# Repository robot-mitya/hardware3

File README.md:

# hardware3
Mitya's III KiCad files

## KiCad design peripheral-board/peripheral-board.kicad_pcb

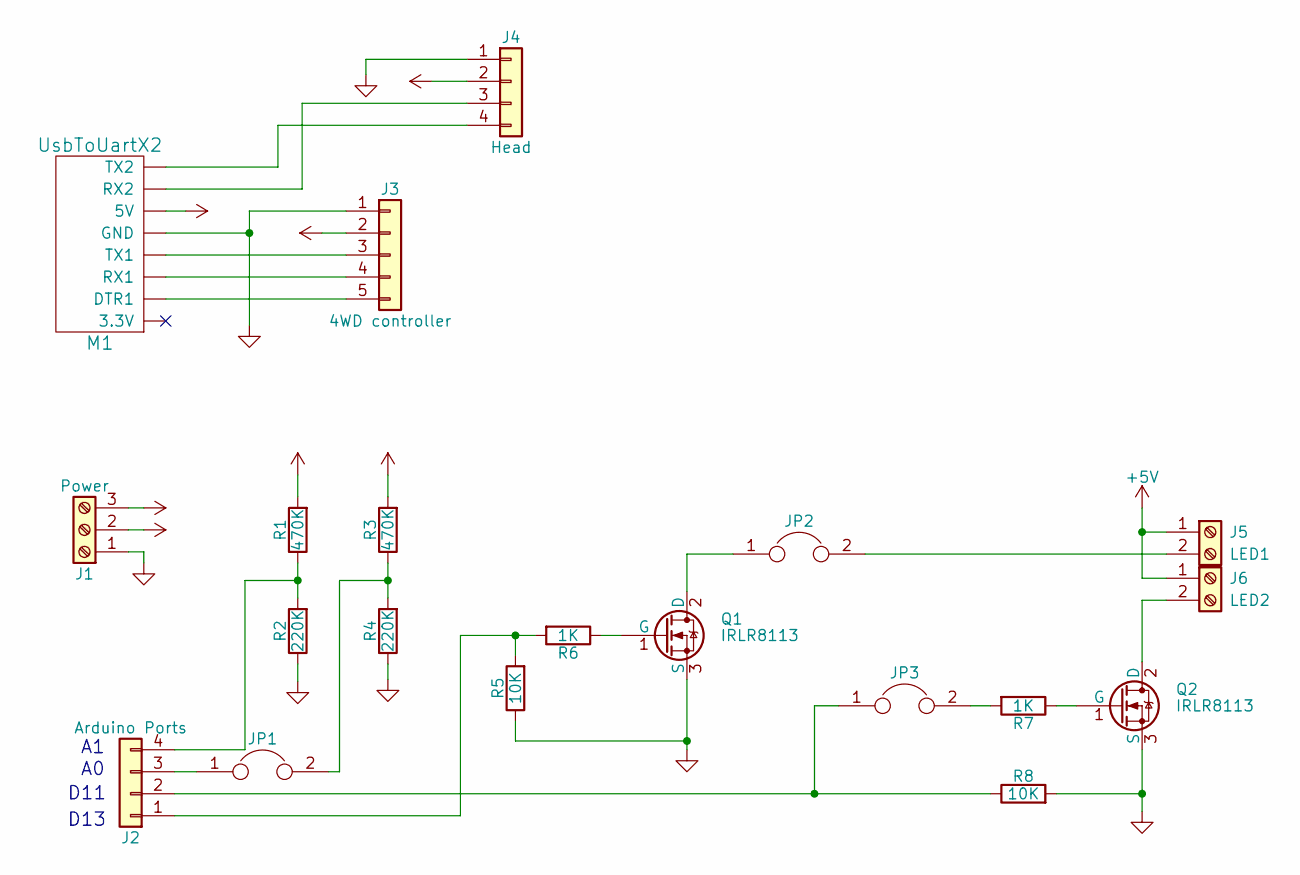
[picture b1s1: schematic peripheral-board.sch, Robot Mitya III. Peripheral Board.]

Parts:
J1: Power; TerminalBlock_Pheonix_PT-3.5mm_3pol
J2: Arduino Ports; JST_EH_B04B-EH-A_04x2.50mm_Straight
J3: 4WD controller; JST_EH_B05B-EH-A_05x2.50mm_Straight
J4: Head; JST_EH_B04B-EH-A_04x2.50mm_Straight
J5: LED1; TerminalBlock_Pheonix_PT-3.5mm_2pol
J6: LED2; TerminalBlock_Pheonix_PT-3.5mm_2pol
JP1, JP2, JP3: Jumper; WireConnection_0.80mmDrill
M1: UsbToUartX2
Q1, Q2: IRLR8113; TO-252-2_Rectifier
R1, R3: 470K; R_1206_HandSoldering
R2, R4: 220K; R_1206_HandSoldering
R5, R8: 10K; R_1206_HandSoldering
R6, R7: 1K; R_1206_HandSoldering

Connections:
+5V: J1.2, J3.2, J5.1, J6.1, M1.6 (5V), R1.2
+7.4V: J1.3, J4.2, R3.2
GND: J1.1, J3.1, J4.1, M1.5 (GND), Q1.3 (S), Q2.3 (S), R2.1, R4.1, R5.1, R8.2
unnamed: J2.1, R5.2, R6.2
unnamed: J2.2, JP3.1, R8.1
unnamed: J2.3, JP1.1
unnamed: J2.4, R1.1, R2.2
unnamed: J3.3, M1.4 (TX1)
unnamed: J3.4, M1.3 (RX1)
unnamed: J3.5, M1.2 (DTR1)
unnamed: J4.3, M1.7 (RX2)
unnamed: J4.4, M1.8 (TX2)
unnamed: J5.2, JP2.2
unnamed: J6.2, Q2.2 (D)
unnamed: JP1.2, R3.1, R4.2
unnamed: JP2.1, Q1.2 (D)
unnamed: JP3.2, R7.2
unnamed: Q1.1 (G), R6.1
unnamed: Q2.1 (G), R7.1

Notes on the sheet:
D13
D11

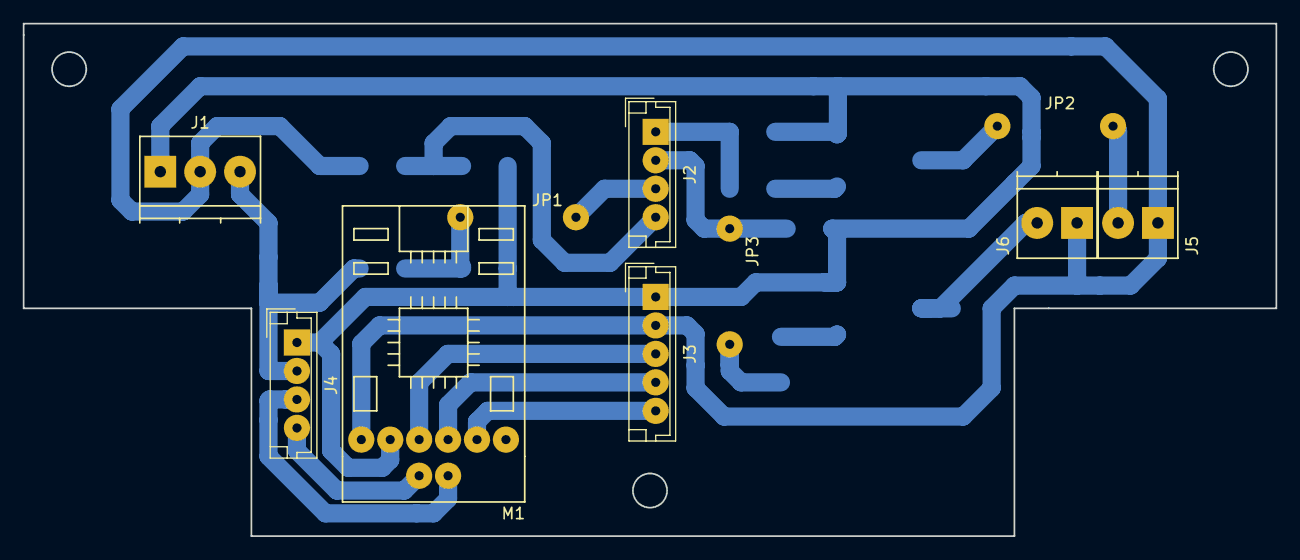
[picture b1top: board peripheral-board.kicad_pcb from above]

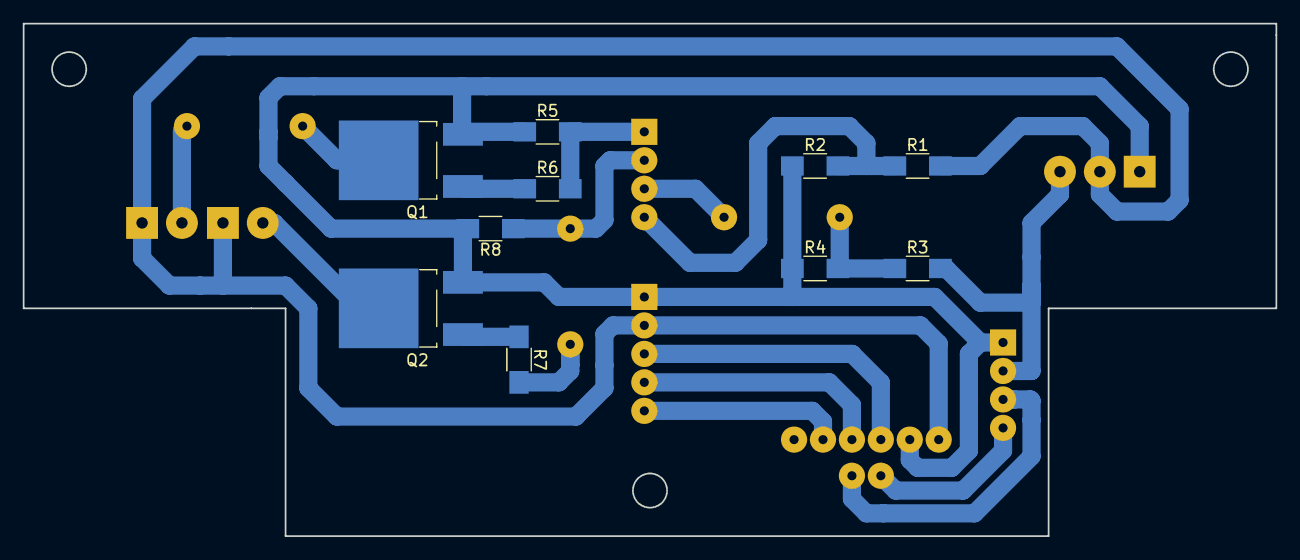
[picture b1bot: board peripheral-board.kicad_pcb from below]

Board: 2 copper layers, 110.0 x 45.0 mm, 20 parts (10 on the bottom side), 19 nets.

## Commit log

2017-11-02 First pcb version
2017-11-05 Refactoring
2017-11-05 Path was fixed
2017-11-05 Terminal blocks were fixed
2017-11-05 Svg results
2017-11-05 Final svg
2017-11-05 F.SilkS.svg
2017-11-05 Final svg with F.SilkS
2017-11-05 Fixes
2017-11-05 Improvements
2017-11-05 Thicker tracks
2017-11-05 Final svg was updated
2017-11-07 Minor changes
2017-11-08 Result svg improvements
